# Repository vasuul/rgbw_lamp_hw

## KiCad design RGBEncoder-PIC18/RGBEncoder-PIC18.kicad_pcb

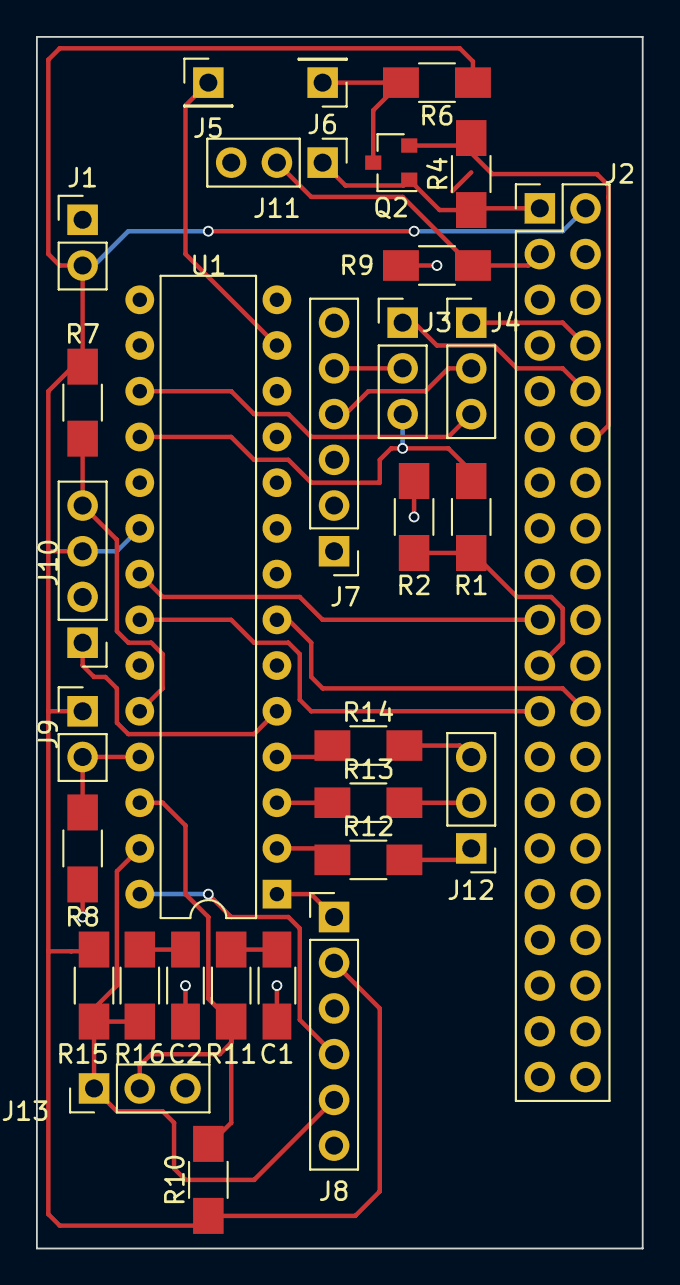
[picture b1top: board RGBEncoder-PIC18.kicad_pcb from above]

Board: 2 copper layers, 33.7 x 67.3 mm, 31 parts (0 on the bottom side), 32 nets.

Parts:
C1, C2: .01uF; C_1206_HandSoldering
J1: Power +5V; Pin_Header_Straight_1x02_Pitch2.54mm
J2: Raspberry_Pi_2_3; Pin_Header_Straight_2x20_Pitch2.54mm
J3: SerialRX; Pin_Header_Straight_1x03_Pitch2.54mm
J4: SerialTX; Pin_Header_Straight_1x03_Pitch2.54mm
J5: FanOn; Pin_Header_Straight_1x01_Pitch2.54mm
J6: LightStrip; Pin_Header_Straight_1x01_Pitch2.54mm
J7: SerialComm; Pin_Header_Straight_1x06_Pitch2.54mm
J8: PICKit; Pin_Header_Straight_1x06_Pitch2.54mm
J9: EncoderBtn; Pin_Header_Straight_1x02_Pitch2.54mm
J10: FrontButton; Pin_Header_Straight_1x04_Pitch2.54mm
J11: TempSensor; Pin_Header_Straight_1x03_Pitch2.54mm
J12: EncoderLED; Pin_Header_Straight_1x03_Pitch2.54mm
J13: EncoderEnc; Pin_Header_Straight_1x03_Pitch2.54mm
Q2: BSS138; SOT-23
R1, R12: 330; R_1206_HandSoldering
R2: 660; R_1206_HandSoldering
R4, R6, R7, R8, R9, R10, R11, R15, R16: 10K; R_1206_HandSoldering
R13, R14: 220; R_1206_HandSoldering
U1: PIC18F2550-ISP; DIP-28_W7.62mm

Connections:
+3V3: J2.1, J11.1, Q2.1, R4.1
+5V: J1.2, J2.2, J8.2, J9.1, J10.3, R6.1, R7.2, R10.1, R15.1, U1.20
/ENC_A: J8.5, J13.1, R15.2, R16.1, U1.27
/ENC_B: J13.2, R10.2, R11.1, U1.26
/ENC_BTN: J9.2, R8.1, U1.25
/ENC_LED_B: R14.1, U1.4
/ENC_LED_G: R13.1, U1.3
/ENC_LED_R: R12.1, U1.2
/FAN_IN: J5.1, U1.13
/FBTN: J10.4, R7.1, U1.24
/FB_CATH: J10.1, U1.5
/MISO: J2.21, R1.1, R2.1
/MOSI: J2.19, U1.21
/PGD: J8.4, U1.28
/PIC_RX: J3.3, R1.2, U1.18
/PIC_TX: J4.3, U1.17
/RPI_RX: J2.10, J3.1
/RPI_TX: J2.8, J4.1
/SCLK: J2.23, U1.22
/SER_RX: J3.2, J7.5
/SER_TX: J4.2, J7.4
/STRIP_OUT: J2.12, Q2.2, R4.2
/TEMP_IN: J2.3, J11.2, R9.2
/VPP/_MCLR: J8.1, U1.1
/_CE0: J2.24, U1.7
GND: C1.2, C2.2, J1.1, J2.6, J2.9, J2.14, J2.20, J2.25, J2.30, J2.34, J2.39, J7.1, J8.3, J10.2, J11.3, J13.3, R2.2, R8.2, R9.1, U1.8, U1.19
unnamed: C1.1, R11.2
unnamed: C2.1, R16.2
unnamed: J6.1, Q2.3, R6.2
unnamed: J12.1, R12.2
unnamed: J12.2, R13.2
unnamed: J12.3, R14.2

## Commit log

2018-02-17 Initial checkin of PIC18 FW code. Please enter the commit message for your changes. Lines starting
2018-02-17 Front button presses only sent on status command. Sending 0 for front button led now turns it off.
2018-02-17 Added KiCad hw files including board and schematic.
